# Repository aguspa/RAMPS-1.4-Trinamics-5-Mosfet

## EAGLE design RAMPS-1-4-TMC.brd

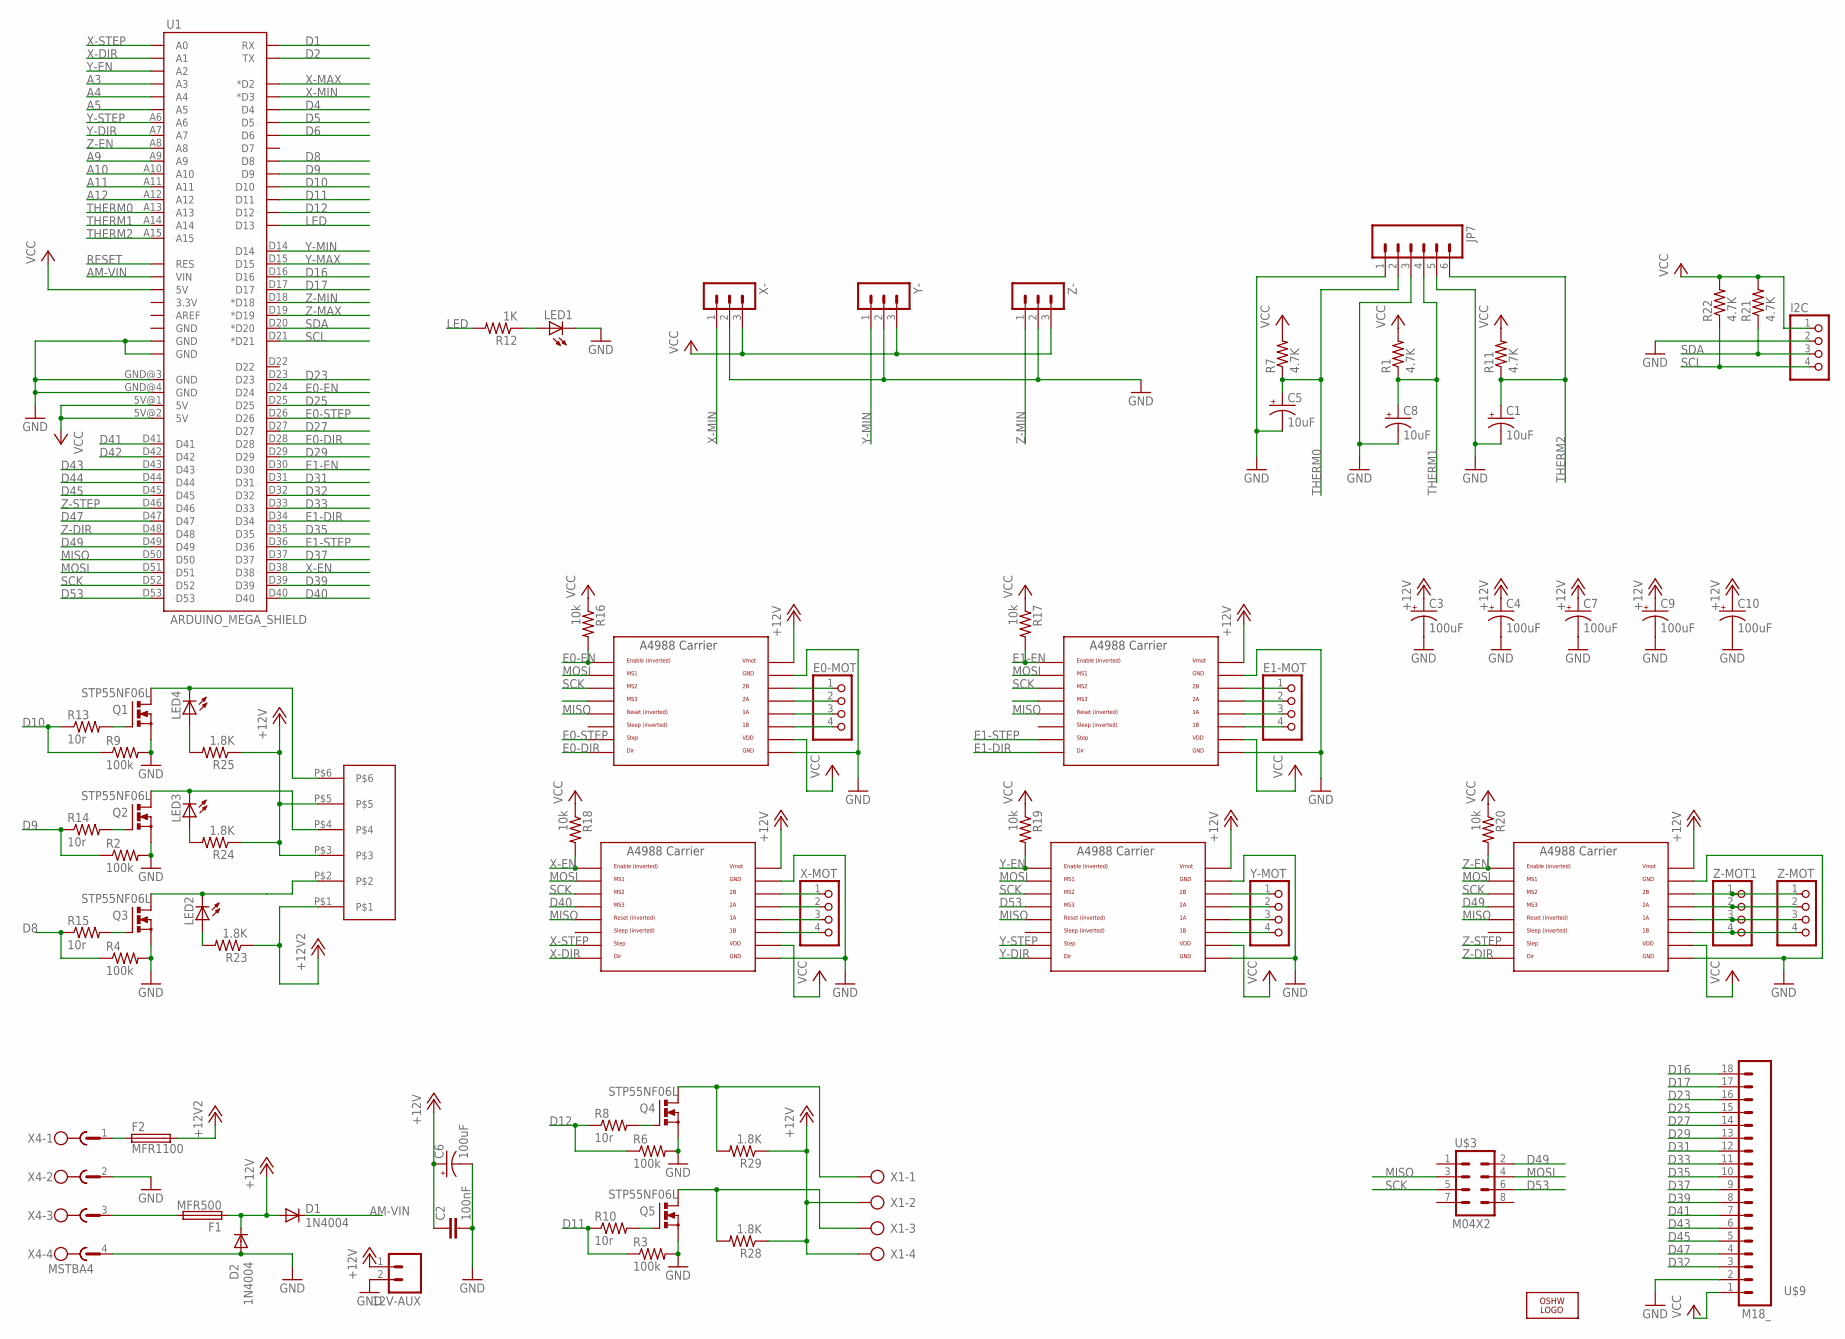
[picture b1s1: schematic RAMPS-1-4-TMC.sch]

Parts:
12V-AUX: M02PTH; 1X02
C1, C5, C8: 10uF; 153CLV-0405
C2: 100nF; C0805
C3, C4, C6, C7, C9, C10: 100uF; 153CLV-0605
D1, D2: 1N4004; DO41-10
E0-MOT, E1-MOT: PINHD-1X4; 1X04
F1: MFR500
F2: MFR1100
I2C: PINHD-1X4; 1X04
JP7: M06SIP; 1X06
LED1, LED2, LED3, LED4: LEDCHIP-LED0805; CHIP-LED0805
LOGO1: OSHW_LOGO_6MILX0100-NT; OSHW_6X100_NOTEXT
Q1, Q2, Q3, Q4, Q5: STP55NF06L; TO220BV
R1, R7, R11, R21, R22: 4.7K; R0805
R2, R3, R4, R6, R9: 100k; R0805
R8, R13, R15: 10r; R0805
R10, R14: 10r; M0805
R12: 1K; R0805
R16, R17, R18, R19, R20: 10k; R0805
R23, R24, R25, R28, R29: 1.8K; R0805
U1: ARDUINO_MEGA_SHIELD
U$2: 282837-6
U$3: M04X2; 2X4
U$4, U$5, U$6, U$7, U$8: A4988BREAKOUT
U$9: M18_; 1X18
X1: AK500/4
X4: MSTBA4
X-: 3PIN-HEADER
X-MOT: PINHD-1X4; 1X04
Y-: 3PIN-HEADER
Y-MOT: PINHD-1X4; 1X04
Z-: 3PIN-HEADER
Z-MOT, Z-MOT1: PINHD-1X4; 1X04

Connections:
+12V: 12V-AUX.1, C2.1, C3.+, C4.+, C6.+, C7.+, C9.+, C10.+, D1.A, D2.C, F1.1, R24.1, R25.1, R28.1, R29.1, U$2.P$3, U$2.P$5, U$4.VMOT, U$5.VMOT, U$6.VMOT, U$7.VMOT, U$8.VMOT, X1.2, X1.4
+12V2: F2.2, R23.1, U$2.P$1
A3: U1.A3
A4: U1.A4
A5: U1.A5
A9: U1.A9
A10: U1.A10
A11: U1.A11
A12: U1.A12
AM-VIN: D1.C, U1.VIN
D1: U1.RX
D2: U1.TX
D4: U1.D4
D5: U1.D5
D6: U1.D6
D8: R4.1, R15.1, U1.D8
D9: R2.1, R14.1, U1.D9
D10: R9.1, R13.1, U1.D10
D11: R3.1, R10.1, U1.D11
D12: R6.1, R8.1, U1.D12
D16: U1.D16, U$9.18
D17: U1.D17, U$9.17
D23: U1.D23, U$9.16
D25: U1.D25, U$9.15
D27: U1.D27, U$9.14
D29: U1.D29, U$9.13
D31: U1.D31, U$9.12
D32: U1.D32, U$9.3
D33: U1.D33, U$9.11
D35: U1.D35, U$9.10
D37: U1.D37, U$9.9
D39: U1.D39, U$9.8
D40: U1.D40, U$6.MS3
D41: U1.D41, U$9.7
D42: U1.D42
D43: U1.D43, U$9.6
D44: U1.D44
D45: U1.D45, U$9.5
D47: U1.D47, U$9.4
D49: U1.D49, U$3.2, U$8.MS3
D53: U1.D53, U$3.6, U$7.MS3
E0-DIR: U1.D28, U$4.DIR
E0-EN: R16.2, U1.D24, U$4.EN
E0-STEP: U1.D26, U$4.STEP
E1-DIR: U1.D34, U$5.DIR
E1-EN: R17.2, U1.D30, U$5.EN
E1-STEP: U1.D36, U$5.STEP
GND: 12V-AUX.2, C1.-, C2.2, C3.-, C4.-, C5.-, C6.-, C7.-, C8.-, C9.-, C10.-, D2.A, I2C.2, JP7.1, JP7.3, JP7.5, LED1.C, Q1.S, Q2.S, Q3.S, Q4.S, Q5.S, R2.2, R3.2, R4.2, R6.2, R9.2, U1.GND@0 (GND), U1.GND@1 (GND), U1.GND@3 (GND), U1.GND@4 (GND), U$4.GND, U$4.GND@0 (GND), U$5.GND, U$5.GND@0 (GND), U$6.GND, U$6.GND@0 (GND), U$7.GND, U$7.GND@0 (GND), U$8.GND, U$8.GND@0 (GND), U$9.2, X4.2, X4.4, X-.2, Y-.2, Z-.2
LED: R12.2, U1.D13
MISO: U1.D50, U$3.3, U$4.RST, U$5.RST, U$6.RST, U$7.RST, U$8.RST
MOSI: U1.D51, U$3.4, U$4.MS1, U$5.MS1, U$6.MS1, U$7.MS1, U$8.MS1
unnamed: LED3.C, Q2.D, U$2.P$4
unnamed: E0-MOT.1, U$4.2B
unnamed: E0-MOT.2, U$4.2A
unnamed: LED4.C, Q1.D, U$2.P$6
unnamed: Q4.D, R29.2, X1.1
unnamed: Q5.G, R10.2
unnamed: E0-MOT.3, U$4.1A
unnamed: E0-MOT.4, U$4.1B
unnamed: E1-MOT.1, U$5.2B
unnamed: E1-MOT.2, U$5.2A
unnamed: Q4.G, R8.2
unnamed: E1-MOT.3, U$5.1A
unnamed: E1-MOT.4, U$5.1B
unnamed: Q5.D, R28.2, X1.3
unnamed: U$6.2B, X-MOT.1
unnamed: U$6.2A, X-MOT.2
unnamed: U$6.1A, X-MOT.3
unnamed: U$6.1B, X-MOT.4
unnamed: U$7.2B, Y-MOT.1
unnamed: U$7.2A, Y-MOT.2
unnamed: U$7.1A, Y-MOT.3
unnamed: LED2.A, R23.2
unnamed: U$7.1B, Y-MOT.4
unnamed: U$8.2B, Z-MOT.1, Z-MOT1.1
unnamed: U$8.2A, Z-MOT.2, Z-MOT1.2
unnamed: U$8.1A, Z-MOT.3, Z-MOT1.3
unnamed: U$8.1B, Z-MOT.4, Z-MOT1.4
unnamed: LED3.A, R24.2
unnamed: LED1.A, R12.1
unnamed: Q2.G, R14.2
unnamed: Q1.G, R13.2
unnamed: Q3.G, R15.2
unnamed: LED4.A, R25.2
unnamed: LED2.C, Q3.D, U$2.P$2
unnamed: F2.1, X4.1
unnamed: F1.2, X4.3
RESET: U1.RES
SCK: U1.D52, U$3.5, U$4.MS2, U$5.MS2, U$6.MS2, U$7.MS2, U$8.MS2
SCL: I2C.4, R22.1, U1.D21 (*D21)
SDA: I2C.3, R21.1, U1.D20 (*D20)
THERM0: C5.+, JP7.2, R7.1, U1.A13
THERM1: C8.+, JP7.4, R1.1, U1.A14
THERM2: C1.+, JP7.6, R11.1, U1.A15
VCC: I2C.1, R1.2, R7.2, R11.2, R16.1, R17.1, R18.1, R19.1, R20.1, R21.2, R22.2, U1.5V@0 (5V), U1.5V@1 (5V), U1.5V@2 (5V), U$4.VDD, U$5.VDD, U$6.VDD, U$7.VDD, U$8.VDD, U$9.1, X-.3, Y-.3, Z-.3
X-DIR: U1.A1, U$6.DIR
X-EN: R18.2, U1.D38, U$6.EN
X-MAX: U1.D2 (*D2)
X-MIN: U1.D3 (*D3), X-.1
X-STEP: U1.A0, U$6.STEP
Y-DIR: U1.A7, U$7.DIR
Y-EN: R19.2, U1.A2, U$7.EN
Y-MAX: U1.D15
Y-MIN: U1.D14, Y-.1
Y-STEP: U1.A6, U$7.STEP
Z-DIR: U1.D48, U$8.DIR
Z-EN: R20.2, U1.A8, U$8.EN
Z-MAX: U1.D19 (*D19)
Z-MIN: U1.D18 (*D18), Z-.1
Z-STEP: U1.D46, U$8.STEP

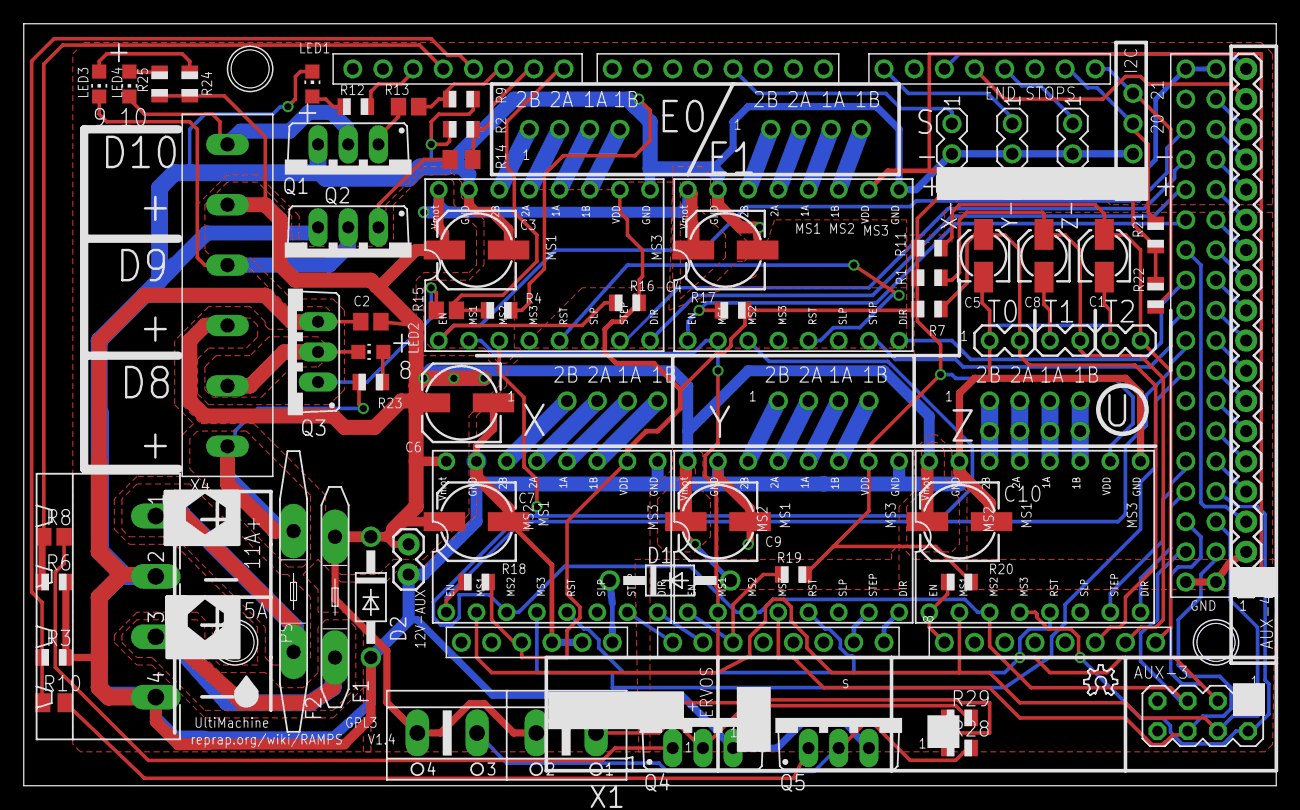
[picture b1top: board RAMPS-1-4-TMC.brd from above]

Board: 2 copper layers, 105.4 x 64.1 mm, 73 parts (0 on the bottom side), 92 nets.

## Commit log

2018-04-01 Initial modified version

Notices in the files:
RAMPS-1-4-TMC.brd:
GPL3
GPL v3
RAMPS-1-4-TMC.sch:
Copyright 2011 Johnny Russell
